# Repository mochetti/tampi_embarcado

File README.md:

# Tampi Embarcado

Programas para o NodeMCU embarcado no Tampi.

Todos os arquivos são compatíveis com a IDE Arduino.

## Contribuição

Todas as sugestões são bem vindas. Caso encontre um bug, fique à vontade para [abrir uma issue](https://github.com/mochetti/tampi_embarcado/issues/new).

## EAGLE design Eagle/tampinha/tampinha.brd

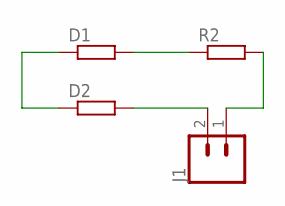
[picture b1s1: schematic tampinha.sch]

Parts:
D1, D2: R-EU_0204/7; 0204/7
J1: CONN_02; 1X02
R2: R-EU_0204/7; 0204/7

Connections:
unnamed: D1.2, R2.1
unnamed: D1.1, D2.1
unnamed: D2.2, J1.2
unnamed: J1.1, R2.2

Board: 2 copper layers, 4 parts (0 on the bottom side), 4 nets, no tracks yet.

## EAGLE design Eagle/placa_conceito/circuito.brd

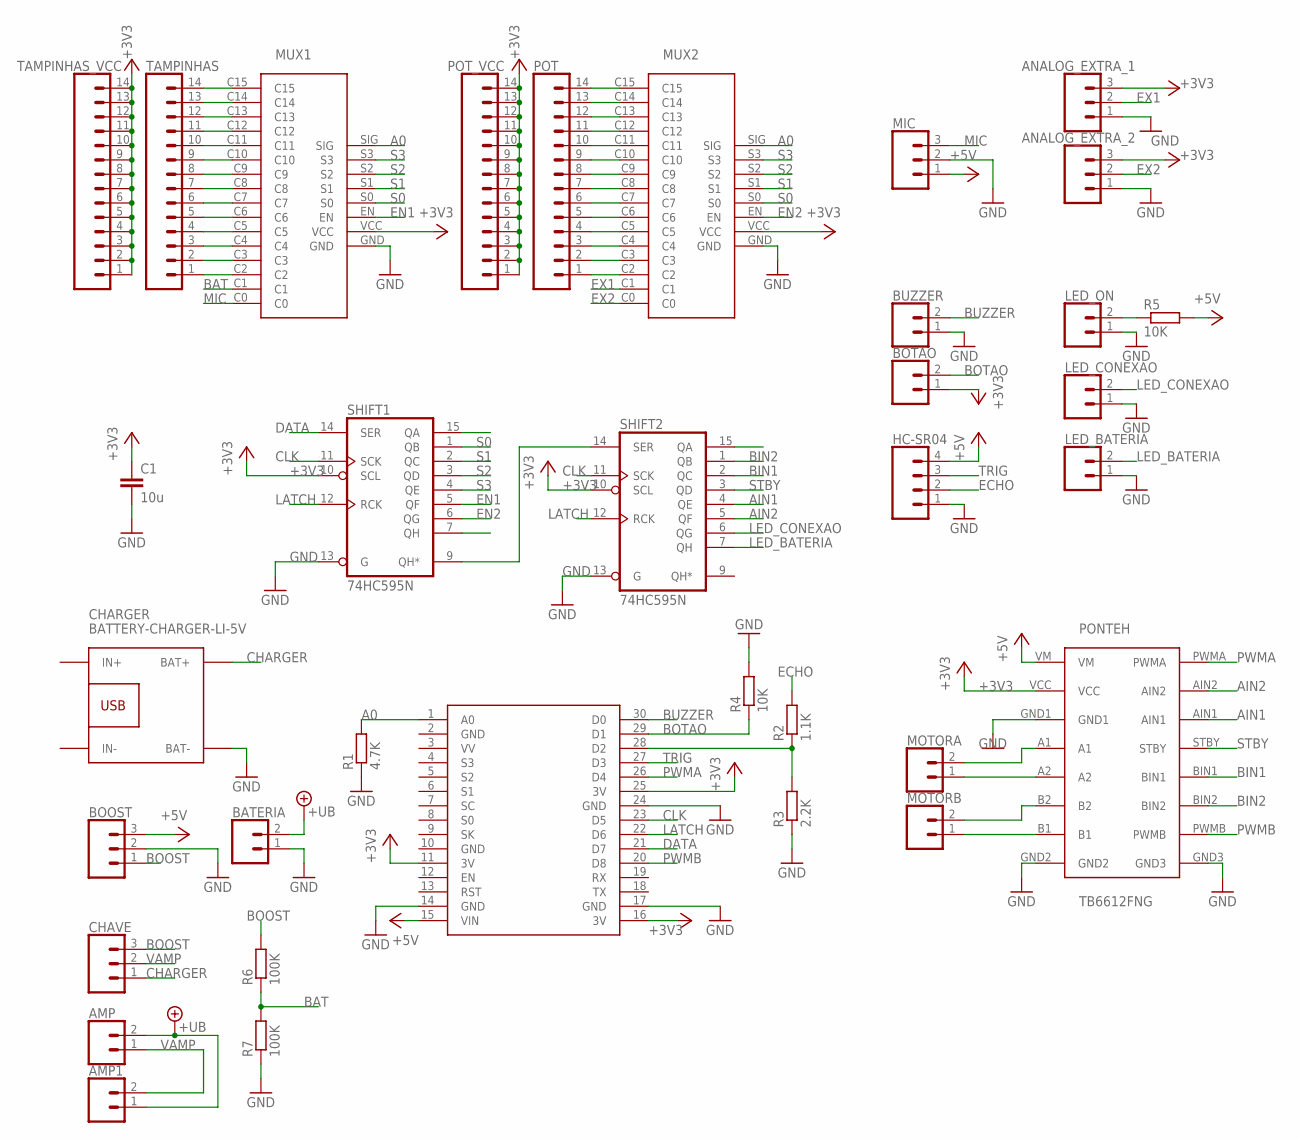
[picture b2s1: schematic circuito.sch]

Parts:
AMP, AMP1: CONN_02; 1X02
ANALOG_EXTRA_1, ANALOG_EXTRA_2: CONN_03; 1X03
BATERIA: CONN_02; 1X02
BOOST: CONN_03; 1X03
BOTAO: CONN_02; 1X02
BUZZER: CONN_02; 1X02
C1: 10u; C2.5-3
CHARGER: BATTERY-CHARGER-LI-5V
CHAVE: CONN_03; 1X03
HC-SR04: CONN_04; 1X04
LED_BATERIA: CONN_02; 1X02
LED_CONEXAO: CONN_02; 1X02
LED_ON: CONN_02; 1X02
MIC: CONN_03; 1X03
MOTORA: CONN_02; 1X02
MOTORB: CONN_02; 1X02
MUX1, MUX2: 4067_MODULE
NODEMCU: NODEMCU
PONTEH: TB6612FNG
POT: CONN_14; 1X14
POT_VCC: CONN_14; 1X14
R1: 4.7K; 0204/7
R2: 1.1K; 0204/7
R3: 2.2K; 0204/7
R4, R5: 10K; 0204/7
R6, R7: 100K; 0204/7
SHIFT1, SHIFT2: 74HC595N; DIL16
TAMPINHAS: CONN_14; 1X14
TAMPINHAS_VCC: CONN_14; 1X14

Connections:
+3V3: ANALOG_EXTRA_1.3, ANALOG_EXTRA_2.3, BOTAO.1, C1.1, MUX1.VCC, MUX2.VCC, NODEMCU.11 (3V), NODEMCU.16 (3V), NODEMCU.25 (3V), PONTEH.VCC, POT_VCC.1, POT_VCC.2, POT_VCC.3, POT_VCC.4, POT_VCC.5, POT_VCC.6, POT_VCC.7, POT_VCC.8, POT_VCC.9, POT_VCC.10, POT_VCC.11, POT_VCC.12, POT_VCC.13, POT_VCC.14, SHIFT1.10 (SCL), SHIFT2.10 (SCL), TAMPINHAS_VCC.1, TAMPINHAS_VCC.2, TAMPINHAS_VCC.3, TAMPINHAS_VCC.4, TAMPINHAS_VCC.5, TAMPINHAS_VCC.6, TAMPINHAS_VCC.7, TAMPINHAS_VCC.8, TAMPINHAS_VCC.9, TAMPINHAS_VCC.10, TAMPINHAS_VCC.11, TAMPINHAS_VCC.12, TAMPINHAS_VCC.13, TAMPINHAS_VCC.14
+5V: BOOST.3, HC-SR04.4, MIC.1, NODEMCU.15 (VIN), PONTEH.VM, R5.2
+UB: AMP.2, AMP1.1, BATERIA.2
A0: MUX1.SIG, MUX2.SIG, NODEMCU.1 (A0), R1.2
AIN1: PONTEH.AIN1, SHIFT2.4 (QE)
AIN2: PONTEH.AIN2, SHIFT2.5 (QF)
BAT: MUX1.C1, R6.1, R7.2
BIN1: PONTEH.BIN1, SHIFT2.2 (QC)
BIN2: PONTEH.BIN2, SHIFT2.1 (QB)
BOOST: BOOST.1, CHAVE.3, R6.2
BOTAO: BOTAO.2, NODEMCU.29 (D1), R4.1
BUZZER: BUZZER.2, NODEMCU.30 (D0)
CHARGER: CHARGER.BAT+, CHAVE.1
CLK: NODEMCU.23 (D5), SHIFT1.11 (SCK), SHIFT2.11 (SCK)
DATA: NODEMCU.21 (D7), SHIFT1.14 (SER)
ECHO: HC-SR04.2, R2.2
EN1: MUX1.EN, SHIFT1.5 (QF)
EN2: MUX2.EN, SHIFT1.6 (QG)
EX1: ANALOG_EXTRA_1.2, MUX2.C1
EX2: ANALOG_EXTRA_2.2, MUX2.C0
GND: ANALOG_EXTRA_1.1, ANALOG_EXTRA_2.1, BATERIA.1, BOOST.2, BUZZER.1, C1.2, CHARGER.BAT-, HC-SR04.1, LED_BATERIA.1, LED_CONEXAO.1, LED_ON.1, MIC.2, MUX1.GND, MUX2.GND, NODEMCU.2 (GND), NODEMCU.10 (GND), NODEMCU.14 (GND), NODEMCU.17 (GND), NODEMCU.24 (GND), PONTEH.GND1, PONTEH.GND2, PONTEH.GND3, R1.1, R3.1, R4.2, R7.1, SHIFT1.8 (GND), SHIFT1.13 (G), SHIFT2.8 (GND), SHIFT2.13 (G)
LATCH: NODEMCU.22 (D6), SHIFT1.12 (RCK), SHIFT2.12 (RCK)
LED_BATERIA: LED_BATERIA.2, SHIFT2.7 (QH)
LED_CONEXAO: LED_CONEXAO.2, SHIFT2.6 (QG)
MIC: MIC.3, MUX1.C0
unnamed: MOTORA.2, PONTEH.A1
unnamed: MOTORA.1, PONTEH.A2
unnamed: MOTORB.2, PONTEH.B2
unnamed: MOTORB.1, PONTEH.B1
unnamed: SHIFT1.9 (QH*), SHIFT2.14 (SER)
unnamed: MUX2.C2, POT.1
unnamed: MUX2.C3, POT.2
unnamed: MUX2.C4, POT.3
unnamed: MUX2.C5, POT.4
unnamed: MUX2.C6, POT.5
unnamed: MUX2.C7, POT.6
unnamed: MUX2.C8, POT.7
unnamed: MUX2.C9, POT.8
unnamed: MUX2.C10, POT.9
unnamed: MUX2.C11, POT.10
unnamed: MUX2.C12, POT.11
unnamed: MUX2.C13, POT.12
unnamed: MUX2.C14, POT.13
unnamed: MUX2.C15, POT.14
unnamed: MUX1.C2, TAMPINHAS.1
unnamed: MUX1.C3, TAMPINHAS.2
unnamed: MUX1.C4, TAMPINHAS.3
unnamed: MUX1.C5, TAMPINHAS.4
unnamed: MUX1.C6, TAMPINHAS.5
unnamed: MUX1.C7, TAMPINHAS.6
unnamed: MUX1.C8, TAMPINHAS.7
unnamed: MUX1.C9, TAMPINHAS.8
unnamed: MUX1.C10, TAMPINHAS.9
unnamed: MUX1.C11, TAMPINHAS.10
unnamed: MUX1.C12, TAMPINHAS.11
unnamed: MUX1.C13, TAMPINHAS.12
unnamed: MUX1.C14, TAMPINHAS.13
unnamed: MUX1.C15, TAMPINHAS.14
unnamed: NODEMCU.28 (D2), R2.1, R3.2
unnamed: LED_ON.2, R5.1
PWMA: NODEMCU.26 (D4), PONTEH.PWMA
PWMB: NODEMCU.20 (D8), PONTEH.PWMB
S0: MUX1.S0, MUX2.S0, SHIFT1.1 (QB)
S1: MUX1.S1, MUX2.S1, SHIFT1.2 (QC)
S2: MUX1.S2, MUX2.S2, SHIFT1.3 (QD)
S3: MUX1.S3, MUX2.S3, SHIFT1.4 (QE)
STBY: PONTEH.STBY, SHIFT2.3 (QD)
TRIG: HC-SR04.3, NODEMCU.27 (D3)
VAMP: AMP.1, AMP1.2, CHAVE.2
VCC: SHIFT1.16 (VCC), SHIFT2.16 (VCC)

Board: 2 copper layers, 35 parts (0 on the bottom side), 70 nets, no tracks yet.

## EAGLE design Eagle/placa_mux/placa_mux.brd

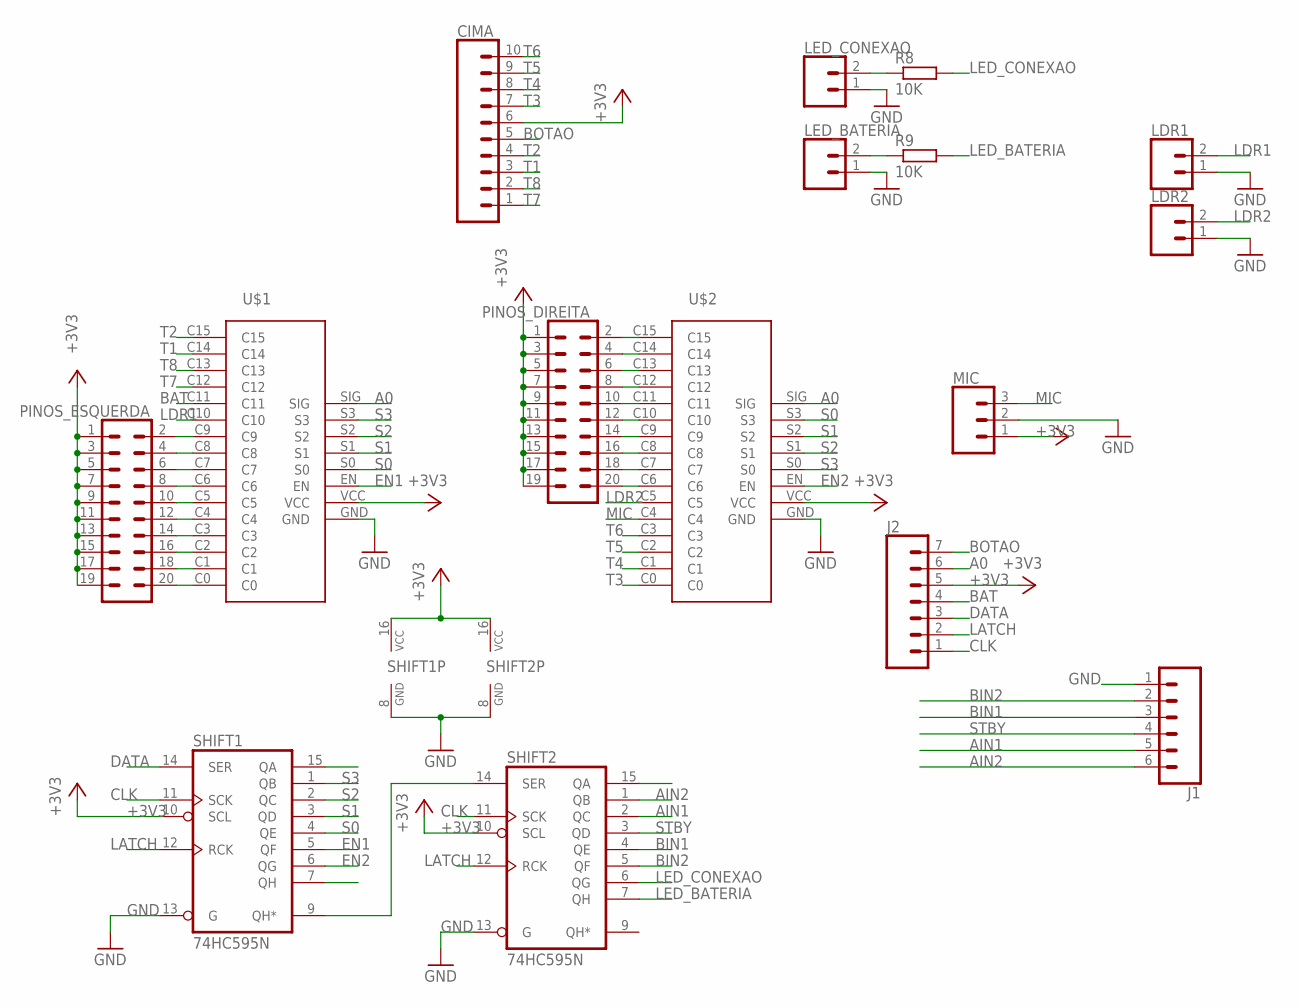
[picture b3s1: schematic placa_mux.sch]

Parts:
CIMA: CONN_10"; 1X10
J1: CONN_06SILK_FEMALE_PTH; 1X06
J2: CONN_07; 1X07
LDR1, LDR2: CONN_02; 1X02
LED_BATERIA: CONN_02; 1X02
LED_CONEXAO: CONN_02; 1X02
MIC: CONN_03; 1X03
PINOS_DIREITA: CONN_10X2; 2X10
PINOS_ESQUERDA: CONN_10X2; 2X10
R8, R9: 10K; 0204/7
SHIFT1, SHIFT2: 74HC595N; DIL16
U$1, U$2: 4067_MODULE

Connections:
+3V3: CIMA.6, J2.5, MIC.1, PINOS_DIREITA.1, PINOS_DIREITA.3, PINOS_DIREITA.5, PINOS_DIREITA.7, PINOS_DIREITA.9, PINOS_DIREITA.11, PINOS_DIREITA.13, PINOS_DIREITA.15, PINOS_DIREITA.17, PINOS_DIREITA.19, PINOS_ESQUERDA.1, PINOS_ESQUERDA.3, PINOS_ESQUERDA.5, PINOS_ESQUERDA.7, PINOS_ESQUERDA.9, PINOS_ESQUERDA.11, PINOS_ESQUERDA.13, PINOS_ESQUERDA.15, PINOS_ESQUERDA.17, PINOS_ESQUERDA.19, SHIFT1.10 (SCL), SHIFT1.16 (VCC), SHIFT2.10 (SCL), SHIFT2.16 (VCC), U$1.VCC, U$2.VCC
A0: J2.6, U$1.SIG, U$2.SIG
AIN1: J1.5, SHIFT2.2 (QC)
AIN2: J1.6, SHIFT2.1 (QB)
BAT: J2.4, U$1.C11
BIN1: J1.3, SHIFT2.4 (QE)
BIN2: J1.2, SHIFT2.5 (QF)
BOTAO: CIMA.5, J2.7
CLK: J2.1, SHIFT1.11 (SCK), SHIFT2.11 (SCK)
DATA: J2.3, SHIFT1.14 (SER)
EN1: SHIFT1.5 (QF), U$1.EN
EN2: SHIFT1.6 (QG), U$2.EN
GND: J1.1, LDR1.1, LDR2.1, LED_BATERIA.1, LED_CONEXAO.1, MIC.2, SHIFT1.8 (GND), SHIFT1.13 (G), SHIFT2.8 (GND), SHIFT2.13 (G), U$1.GND, U$2.GND
LATCH: J2.2, SHIFT1.12 (RCK), SHIFT2.12 (RCK)
LDR1: LDR1.2, U$1.C10
LDR2: LDR2.2, U$2.C5
LED_BATERIA: R9.2, SHIFT2.7 (QH)
LED_CONEXAO: R8.2, SHIFT2.6 (QG)
MIC: MIC.3, U$2.C4
unnamed: PINOS_ESQUERDA.2, U$1.C9
unnamed: PINOS_ESQUERDA.4, U$1.C8
unnamed: PINOS_ESQUERDA.6, U$1.C7
unnamed: PINOS_ESQUERDA.8, U$1.C6
unnamed: SHIFT1.9 (QH*), SHIFT2.14 (SER)
unnamed: PINOS_ESQUERDA.10, U$1.C5
unnamed: PINOS_ESQUERDA.12, U$1.C4
unnamed: PINOS_DIREITA.2, U$2.C15
unnamed: PINOS_DIREITA.4, U$2.C14
unnamed: PINOS_DIREITA.6, U$2.C13
unnamed: PINOS_DIREITA.8, U$2.C12
unnamed: PINOS_DIREITA.10, U$2.C11
unnamed: PINOS_DIREITA.12, U$2.C10
unnamed: PINOS_DIREITA.14, U$2.C9
unnamed: PINOS_DIREITA.16, U$2.C8
unnamed: PINOS_DIREITA.18, U$2.C7
unnamed: PINOS_DIREITA.20, U$2.C6
unnamed: PINOS_ESQUERDA.14, U$1.C3
unnamed: PINOS_ESQUERDA.16, U$1.C2
unnamed: PINOS_ESQUERDA.18, U$1.C1
unnamed: PINOS_ESQUERDA.20, U$1.C0
unnamed: LED_CONEXAO.2, R8.1
unnamed: LED_BATERIA.2, R9.1
S0: SHIFT1.4 (QE), U$1.S0, U$2.S3
S1: SHIFT1.3 (QD), U$1.S1, U$2.S2
S2: SHIFT1.2 (QC), U$1.S2, U$2.S1
S3: SHIFT1.1 (QB), U$1.S3, U$2.S0
STBY: J1.4, SHIFT2.3 (QD)
T1: CIMA.3, U$1.C14
T2: CIMA.4, U$1.C15
T3: CIMA.7, U$2.C0
T4: CIMA.8, U$2.C1
T5: CIMA.9, U$2.C2
T6: CIMA.10, U$2.C3
T7: CIMA.1, U$1.C12
T8: CIMA.2, U$1.C13

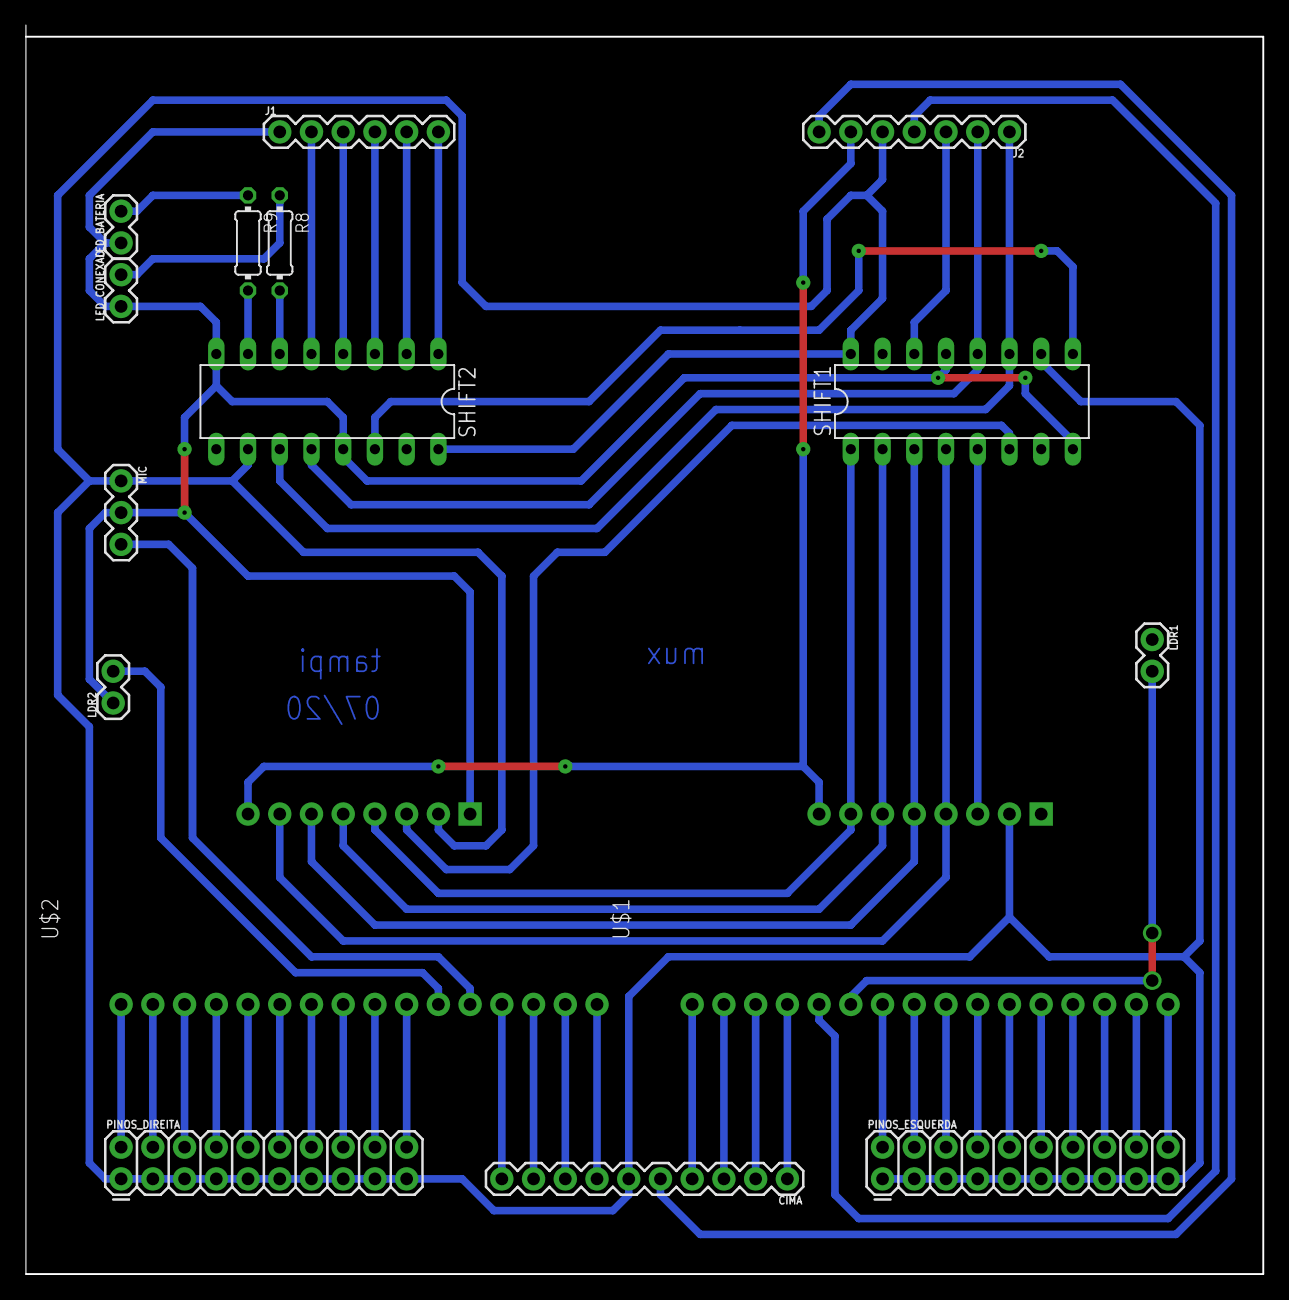
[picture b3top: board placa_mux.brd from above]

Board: 2 copper layers, 99.1 x 100.0 mm, 16 parts (0 on the bottom side), 55 nets.

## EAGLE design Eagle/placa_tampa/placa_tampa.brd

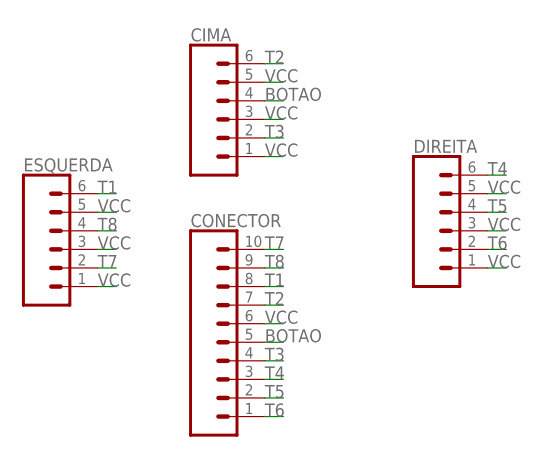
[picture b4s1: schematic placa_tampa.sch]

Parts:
CIMA: CONN_06SILK_FEMALE_PTH; 1X06
CONECTOR: CONN_10"; 1X10
DIREITA: CONN_06SILK_FEMALE_PTH; 1X06
ESQUERDA: CONN_06SILK_FEMALE_PTH; 1X06

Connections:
BOTAO: CIMA.4, CONECTOR.5
T1: CONECTOR.8, ESQUERDA.6
T2: CIMA.6, CONECTOR.7
T3: CIMA.2, CONECTOR.4
T4: CONECTOR.3, DIREITA.6
T5: CONECTOR.2, DIREITA.4
T6: CONECTOR.1, DIREITA.2
T7: CONECTOR.10, ESQUERDA.2
T8: CONECTOR.9, ESQUERDA.4
VCC: CIMA.1, CIMA.3, CIMA.5, CONECTOR.6, DIREITA.1, DIREITA.3, DIREITA.5, ESQUERDA.1, ESQUERDA.3, ESQUERDA.5

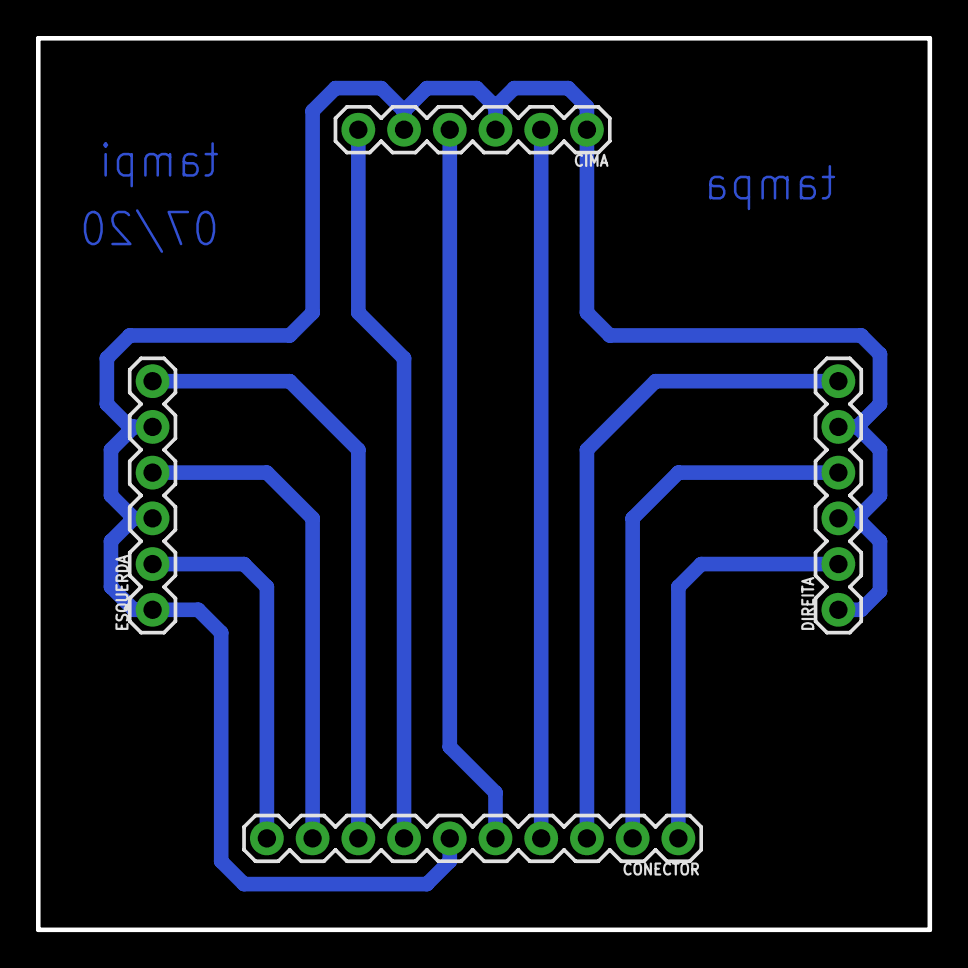
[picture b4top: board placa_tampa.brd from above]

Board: 2 copper layers, 49.5 x 49.5 mm, 4 parts (0 on the bottom side), 10 nets.

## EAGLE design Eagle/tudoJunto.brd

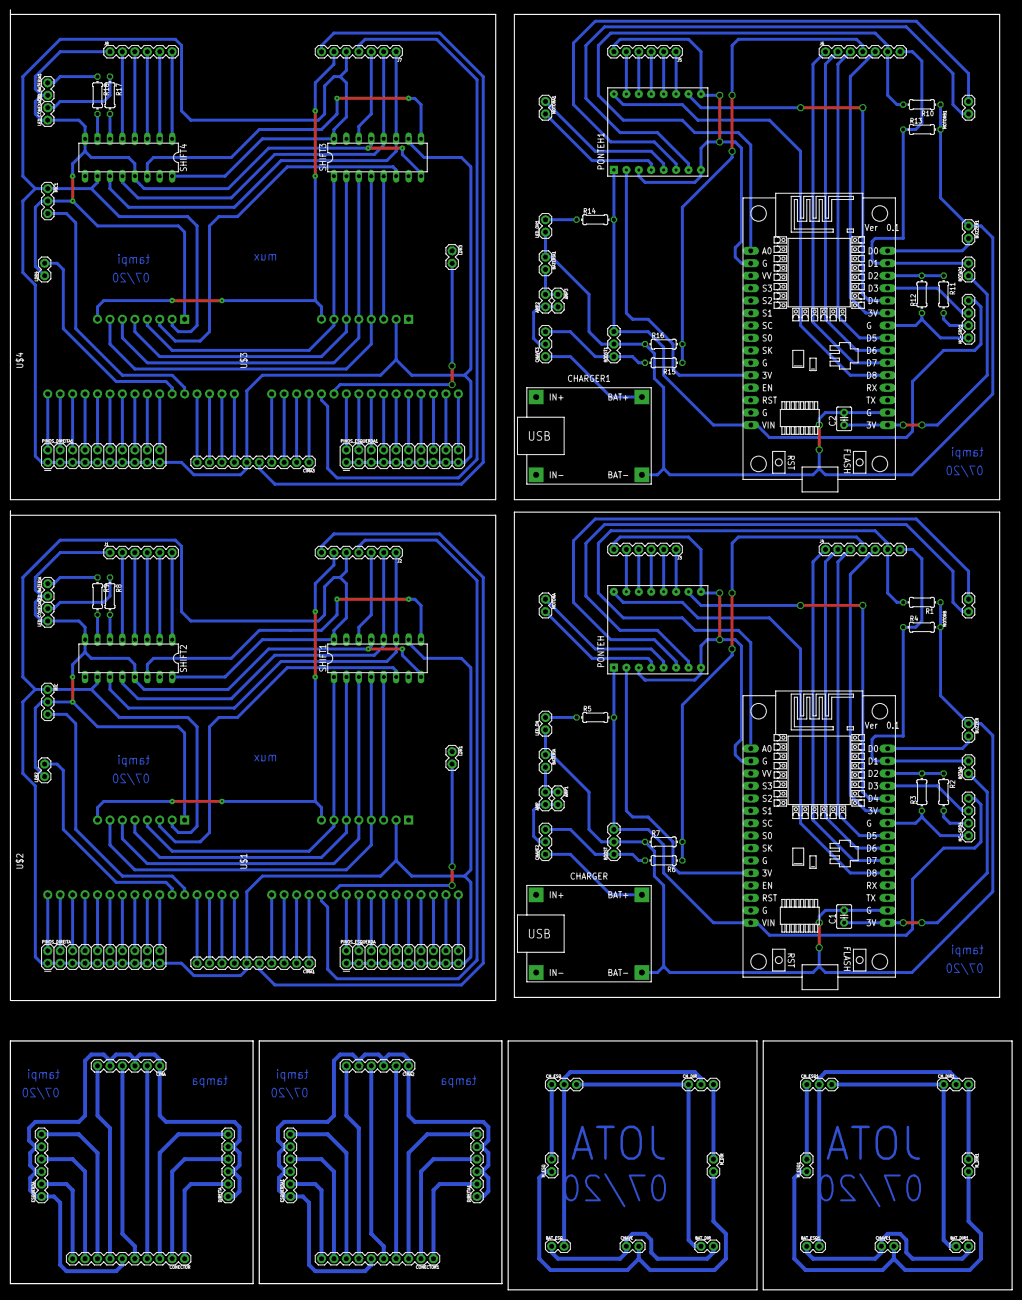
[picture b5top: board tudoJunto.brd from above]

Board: 2 copper layers, 204.5 x 261.3 mm, 102 parts (0 on the bottom side), 200 nets.

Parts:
AMP, AMP1, AMP2, AMP3: 1X02
BATERIA, BATERIA1: 1X02
BAT_DIR, BAT_DIR1: 1X02
BAT_ESQ, BAT_ESQ1: 1X02
BOOST, BOOST1: 1X03
BOTAO, BOTAO1: 1X02
BUZZER, BUZZER1: 1X02
C1, C2: 10u; C2.5-3
CHARGER, CHARGER1: BATTERY-CHARGER-LI-5V
CHAVE, CHAVE1: 1X02
CHAVE2, CHAVE3: 1X03
CH_DIR, CH_DIR1: 1X03
CH_ESQ, CH_ESQ1: 1X03
CIMA, CIMA2: 1X06
CIMA1, CIMA3: 1X10
CONECTOR, CONECTOR1: 1X10
DIREITA, DIREITA1: 1X06
ESQUERDA, ESQUERDA1: 1X06
HC-SR01, HC-SR04: 1X04
J1, J3, J5, J8: 1X06
J2, J4, J6, J7: 1X07
LDR1, LDR2, LDR3, LDR4: 1X02
LED_BATERIA, LED_BATERIA1: 1X02
LED_CONEXAO, LED_CONEXAO1: 1X02
LED_ON, LED_ON1: 1X02
MIC, MIC1: 1X03
MOTORA, MOTORA1: 1X02
MOTORB, MOTORB1: 1X02
M_DIR, M_DIR1: 1X02
M_ESQ, M_ESQ1: 1X02
NODEMCU, NODEMCU1: NODEMCU
PINOS_DIREITA, PINOS_DIREITA1: 2X10
PINOS_ESQUERDA, PINOS_ESQUERDA1: 2X10
PONTEH, PONTEH1: TB6612FNG
R1, R10: 4.7K; 0204/7
R2, R11: 1.1K; 0204/7
R3, R12: 2.2K; 0204/7
R4, R5, R8, R9, R13, R14, R17, R18: 10K; 0204/7
R6, R7, R15, R16: 100K; 0204/7
SHIFT1, SHIFT2, SHIFT3, SHIFT4: 74HC595N; DIL16
U$1, U$2, U$3, U$4: 4067_MODULE

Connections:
+3V1: BOTAO.1, C1.1, J4.5, NODEMCU.11, NODEMCU.16, NODEMCU.25, PONTEH.VCC
+3V2: BOTAO1.1, C2.1, J6.5, NODEMCU1.11, NODEMCU1.16, NODEMCU1.25, PONTEH1.VCC
+3V3: CIMA1.6, J2.5, MIC.1, PINOS_DIREITA.1, PINOS_DIREITA.3, PINOS_DIREITA.5, PINOS_DIREITA.7, PINOS_DIREITA.9, PINOS_DIREITA.11, PINOS_DIREITA.13, PINOS_DIREITA.15, PINOS_DIREITA.17, PINOS_DIREITA.19, PINOS_ESQUERDA.1, PINOS_ESQUERDA.3, PINOS_ESQUERDA.5, PINOS_ESQUERDA.7, PINOS_ESQUERDA.9, PINOS_ESQUERDA.11, PINOS_ESQUERDA.13, PINOS_ESQUERDA.15, PINOS_ESQUERDA.17, PINOS_ESQUERDA.19, SHIFT1.10, SHIFT1.16, SHIFT2.10, SHIFT2.16, U$1.VCC, U$2.VCC
+3V4: CIMA3.6, J7.5, MIC1.1, PINOS_DIREITA1.1, PINOS_DIREITA1.3, PINOS_DIREITA1.5, PINOS_DIREITA1.7, PINOS_DIREITA1.9, PINOS_DIREITA1.11, PINOS_DIREITA1.13, PINOS_DIREITA1.15, PINOS_DIREITA1.17, PINOS_DIREITA1.19, PINOS_ESQUERDA1.1, PINOS_ESQUERDA1.3, PINOS_ESQUERDA1.5, PINOS_ESQUERDA1.7, PINOS_ESQUERDA1.9, PINOS_ESQUERDA1.11, PINOS_ESQUERDA1.13, PINOS_ESQUERDA1.15, PINOS_ESQUERDA1.17, PINOS_ESQUERDA1.19, SHIFT3.10, SHIFT3.16, SHIFT4.10, SHIFT4.16, U$3.VCC, U$4.VCC
+5V: BOOST.3, HC-SR04.4, NODEMCU.15, PONTEH.VM, R5.2
+5V1: BOOST1.3, HC-SR01.4, NODEMCU1.15, PONTEH1.VM, R14.2
+UB: AMP.2, AMP1.1, BATERIA.2
+UB1: AMP2.2, AMP3.1, BATERIA1.2
A0: J2.6, U$1.SIG, U$2.SIG
A1: J4.6, NODEMCU.1, R1.2
A2: J6.6, NODEMCU1.1, R10.2
A3: J7.6, U$3.SIG, U$4.SIG
AIN1: J1.5, SHIFT2.2
AIN2: J1.6, SHIFT2.1
AIN3: J3.5, PONTEH.AIN2
AIN4: J3.4, PONTEH.AIN1
AIN5: J5.5, PONTEH1.AIN2
AIN6: J5.4, PONTEH1.AIN1
AIN7: J8.6, SHIFT4.1
AIN8: J8.5, SHIFT4.2
BAT: J2.4, U$1.C11
BAT1: J4.4, R6.1, R7.2
BAT2: J6.4, R15.1, R16.2
BAT3: J7.4, U$3.C11
BIN1: J1.3, SHIFT2.4
BIN2: J1.2, SHIFT2.5
BIN3: J3.2, PONTEH.BIN1
BIN4: J3.1, PONTEH.BIN2
BIN5: J5.2, PONTEH1.BIN1
BIN6: J5.1, PONTEH1.BIN2
BIN7: J8.3, SHIFT4.4
BIN8: J8.2, SHIFT4.5
BOOST: BOOST.1, CHAVE2.3, R6.2
BOOST1: BOOST1.1, CHAVE3.3, R15.2
BOTAO: CIMA.4, CONECTOR.5
BOTAO1: CIMA1.5, J2.7
BOTAO2: CIMA2.4, CONECTOR1.5
BOTAO3: BOTAO.2, J4.7, NODEMCU.29, R4.1
BOTAO4: BOTAO1.2, J6.7, NODEMCU1.29, R13.1
BOTAO5: CIMA3.5, J7.7
BUZZER: BUZZER.2, NODEMCU.30
BUZZER1: BUZZER1.2, NODEMCU1.30
CHARGER: CHARGER.BAT+, CHAVE2.1
CHARGER1: CHARGER1.BAT+, CHAVE3.1
CLK: J2.1, SHIFT1.11, SHIFT2.11
CLK1: J4.1, NODEMCU.21
CLK2: J6.1, NODEMCU1.21
CLK3: J7.1, SHIFT3.11, SHIFT4.11
DATA: J2.3, SHIFT1.14
DATA1: J4.3, NODEMCU.23
DATA2: J6.3, NODEMCU1.23
DATA3: J7.3, SHIFT3.14
ECHO: HC-SR04.2, R2.2
ECHO1: HC-SR01.2, R11.2
EN1: SHIFT1.5, U$1.EN
EN2: SHIFT1.6, U$2.EN
EN3: SHIFT3.5, U$3.EN
EN4: SHIFT3.6, U$4.EN
GND1: J1.1, LDR1.1, LDR2.1, LED_BATERIA.1, LED_CONEXAO.1, MIC.2, SHIFT1.8, SHIFT1.13, SHIFT2.8, SHIFT2.13, U$1.GND, U$2.GND
GND5: BATERIA.1, BOOST.2, BUZZER.1, C1.2, CHARGER.BAT-, HC-SR04.1, J3.6, LED_ON.1, NODEMCU.2, NODEMCU.10, NODEMCU.14, NODEMCU.17, NODEMCU.24, PONTEH.GND1, PONTEH.GND2, PONTEH.GND3, R1.1, R3.1, R4.2, R7.1
GND6: BATERIA1.1, BOOST1.2, BUZZER1.1, C2.2, CHARGER1.BAT-, HC-SR01.1, J5.6, LED_ON1.1, NODEMCU1.2, NODEMCU1.10, NODEMCU1.14, NODEMCU1.17, NODEMCU1.24, PONTEH1.GND1, PONTEH1.GND2, PONTEH1.GND3, R10.1, R12.1, R13.2, R16.1
GND7: J8.1, LDR3.1, LDR4.1, LED_BATERIA1.1, LED_CONEXAO1.1, MIC1.2, SHIFT3.8, SHIFT3.13, SHIFT4.8, SHIFT4.13, U$3.GND, U$4.GND
LATCH: J2.2, SHIFT1.12, SHIFT2.12
LATCH1: J4.2, NODEMCU.22
LATCH2: J6.2, NODEMCU1.22
LATCH3: J7.2, SHIFT3.12, SHIFT4.12
LDR1: LDR1.2, U$1.C10
LDR2: LDR2.2, U$2.C5
LDR3: LDR3.2, U$3.C10
LDR4: LDR4.2, U$4.C5
LED_BATERIA: R9.2, SHIFT2.7
LED_BATERIA1: R18.2, SHIFT4.7
LED_CONEXAO: R8.2, SHIFT2.6
LED_CONEXAO1: R17.2, SHIFT4.6
MIC: MIC.3, U$2.C4
MIC1: MIC1.3, U$4.C4
unnamed: PINOS_ESQUERDA.2, U$1.C9
unnamed: PINOS_ESQUERDA.4, U$1.C8
unnamed: PINOS_ESQUERDA.6, U$1.C7
unnamed: PINOS_ESQUERDA.8, U$1.C6
unnamed: SHIFT1.9, SHIFT2.14
unnamed: PINOS_ESQUERDA.10, U$1.C5
unnamed: PINOS_ESQUERDA.12, U$1.C4
unnamed: PINOS_DIREITA.2, U$2.C15
unnamed: PINOS_DIREITA.4, U$2.C14
unnamed: PINOS_DIREITA.6, U$2.C13
unnamed: PINOS_DIREITA.8, U$2.C12
unnamed: PINOS_DIREITA.10, U$2.C11
unnamed: PINOS_DIREITA.12, U$2.C10
unnamed: PINOS_DIREITA.14, U$2.C9
unnamed: PINOS_DIREITA.16, U$2.C8
unnamed: PINOS_DIREITA.18, U$2.C7
unnamed: PINOS_DIREITA.20, U$2.C6
unnamed: PINOS_ESQUERDA.14, U$1.C3
unnamed: PINOS_ESQUERDA.16, U$1.C2
unnamed: PINOS_ESQUERDA.18, U$1.C1
unnamed: PINOS_ESQUERDA.20, U$1.C0
unnamed: LED_CONEXAO.2, R8.1
unnamed: LED_BATERIA.2, R9.1
unnamed: BAT_ESQ.2, CH_DIR.2, CH_ESQ.2
unnamed: BAT_DIR.1, CH_DIR.1, CH_ESQ.3
unnamed: CH_DIR.3, M_DIR.1
unnamed: CH_ESQ.1, M_ESQ.2
unnamed: CHAVE.2, M_DIR.2, M_ESQ.1
unnamed: BAT_DIR.2, BAT_ESQ.1, CHAVE.1
unnamed: BAT_ESQ1.2, CH_DIR1.2, CH_ESQ1.2
unnamed: BAT_DIR1.1, CH_DIR1.1, CH_ESQ1.3
unnamed: CH_DIR1.3, M_DIR1.1
unnamed: CH_ESQ1.1, M_ESQ1.2
unnamed: CHAVE1.2, M_DIR1.2, M_ESQ1.1
unnamed: BAT_DIR1.2, BAT_ESQ1.1, CHAVE1.1
unnamed: MOTORB.2, PONTEH.B2
unnamed: MOTORB.1, PONTEH.B1
unnamed: MOTORA.2, PONTEH.A1
unnamed: MOTORA.1, PONTEH.A2
unnamed: NODEMCU.28, R2.1, R3.2
unnamed: LED_ON.2, R5.1
unnamed: MOTORB1.2, PONTEH1.B2
unnamed: MOTORB1.1, PONTEH1.B1
unnamed: MOTORA1.2, PONTEH1.A1
unnamed: MOTORA1.1, PONTEH1.A2
unnamed: NODEMCU1.28, R11.1, R12.2
unnamed: LED_ON1.2, R14.1
unnamed: SHIFT3.9, SHIFT4.14
unnamed: PINOS_ESQUERDA1.2, U$3.C9
unnamed: PINOS_ESQUERDA1.4, U$3.C8
unnamed: PINOS_ESQUERDA1.6, U$3.C7
unnamed: PINOS_ESQUERDA1.8, U$3.C6
unnamed: PINOS_ESQUERDA1.10, U$3.C5
unnamed: PINOS_ESQUERDA1.12, U$3.C4
unnamed: PINOS_ESQUERDA1.14, U$3.C3
unnamed: PINOS_ESQUERDA1.16, U$3.C2
unnamed: PINOS_ESQUERDA1.18, U$3.C1
unnamed: PINOS_ESQUERDA1.20, U$3.C0
unnamed: PINOS_DIREITA1.2, U$4.C15
unnamed: PINOS_DIREITA1.4, U$4.C14
unnamed: PINOS_DIREITA1.6, U$4.C13
unnamed: PINOS_DIREITA1.8, U$4.C12
unnamed: PINOS_DIREITA1.10, U$4.C11
unnamed: PINOS_DIREITA1.12, U$4.C10
unnamed: PINOS_DIREITA1.14, U$4.C9
unnamed: PINOS_DIREITA1.16, U$4.C8
unnamed: PINOS_DIREITA1.18, U$4.C7
unnamed: PINOS_DIREITA1.20, U$4.C6
unnamed: LED_CONEXAO1.2, R17.1
unnamed: LED_BATERIA1.2, R18.1
PWMA: NODEMCU.20, PONTEH.PWMA
PWMA1: NODEMCU1.20, PONTEH1.PWMA
PWMB: NODEMCU.26, PONTEH.PWMB
PWMB1: NODEMCU1.26, PONTEH1.PWMB
S0: SHIFT1.4, U$1.S0, U$2.S3
S1: SHIFT1.3, U$1.S1, U$2.S2
S2: SHIFT1.2, U$1.S2, U$2.S1
S3: SHIFT1.1, U$1.S3, U$2.S0
S4: SHIFT3.1, U$3.S3, U$4.S0
S5: SHIFT3.2, U$3.S2, U$4.S1
S6: SHIFT3.3, U$3.S1, U$4.S2
S7: SHIFT3.4, U$3.S0, U$4.S3
STBY: J1.4, SHIFT2.3
STBY1: J3.3, PONTEH.STBY
STBY2: J5.3, PONTEH1.STBY
STBY3: J8.4, SHIFT4.3
T1: CONECTOR.8, ESQUERDA.6
T2: CIMA.6, CONECTOR.7
T3: CIMA.2, CONECTOR.4
T4: CONECTOR.3, DIREITA.6
T5: CONECTOR.2, DIREITA.4
T6: CONECTOR.1, DIREITA.2
T7: CONECTOR.10, ESQUERDA.2
T8: CONECTOR.9, ESQUERDA.4
T9: CIMA1.10, U$2.C3
T10: CIMA1.9, U$2.C2
T11: CIMA1.8, U$2.C1
T12: CIMA1.7, U$2.C0
T13: CIMA1.4, U$1.C15
T14: CIMA1.3, U$1.C14
T15: CIMA1.2, U$1.C13
T16: CIMA1.1, U$1.C12
T17: CONECTOR1.10, ESQUERDA1.2
T18: CONECTOR1.8, ESQUERDA1.6
T19: CIMA2.6, CONECTOR1.7
T20: CIMA2.2, CONECTOR1.4
T21: CONECTOR1.3, DIREITA1.6
T22: CONECTOR1.2, DIREITA1.4
T23: CONECTOR1.1, DIREITA1.2
T24: CONECTOR1.9, ESQUERDA1.4
T25: CIMA3.10, U$4.C3
T26: CIMA3.9, U$4.C2
T27: CIMA3.8, U$4.C1
T28: CIMA3.7, U$4.C0
T29: CIMA3.4, U$3.C15
T30: CIMA3.3, U$3.C14
T31: CIMA3.2, U$3.C13
T32: CIMA3.1, U$3.C12
TRIG: HC-SR04.3, NODEMCU.27
TRIG1: HC-SR01.3, NODEMCU1.27
VAMP: AMP.1, AMP1.2, CHAVE2.2
VAMP1: AMP2.1, AMP3.2, CHAVE3.2
VCC: CIMA.1, CIMA.3, CIMA.5, CONECTOR.6, DIREITA.1, DIREITA.3, DIREITA.5, ESQUERDA.1, ESQUERDA.3, ESQUERDA.5
VCC1: CIMA2.1, CIMA2.3, CIMA2.5, CONECTOR1.6, DIREITA1.1, DIREITA1.3, DIREITA1.5, ESQUERDA1.1, ESQUERDA1.3, ESQUERDA1.5

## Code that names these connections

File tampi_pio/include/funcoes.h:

#ifndef FUNCOES_H
#define FUNCOES_H

#include "Arduino.h"
#include <ESP8266WiFi.h>            // bibliotecas do servidor          
#include <WebSocketsServer.h>
// #include <WebSocketsClient.h>

// Pinos do NodeMCU

const int pwmEsq = D4;  // pinos digitais no ESP
const int pwmDir = D8;

const int echoPin = D2;  // echo do ultrassonico
const int trigPin = D3;  // trig do ultrassonico

const int dataPin = D5;  // dados seriais do 74595
const int latchPin = D6; // latch do 74595
const int clkPin = D7;   // clk do 74595

const int buzzerPin = D0;

const int botaoPin = D1;    // botao
const int analogPin = A0;  // pino analogico

// Pinos dos shifts

const int A4067 = 27;
const int B4067 = 28;
const int C4067 = 29;
const int D4067 = 30;
const int E4067 = 26;
const int F4067 = 25;

const int ledsTopo[] = {
  16, 17, 18, 19, 20, 21, 22, 23
};
const int ledsEsq[] = {
  38, 37, 36, 35, 34, 33
};
const int ledsDir[] = {
  14, 13, 12, 11, 10, 9
};

const int AIN2 = 4;
const int AIN1 = 3;
const int STDBY = 2;
const int BIN1 = 1;
const int BIN2 = 0;

const int redPin = 7;
const int greenPin = 6;
const int bluePin = 5;

const int farolPin = 24;
const int irEsqLED = 39;
const int irDirLED = 15;
const int setaEsqPin = 32;
const int setaDirPin = 8;

// Pinos dos mux

const int batPin = 1;
const int micPin = 16;
const int ldrEsqPin = 0;
const int ldrDirPin = 25;
const int encEsqPin = 2;
const int encDirPin = 23;
const int irEsqAnalog = 3;
const int irDirAnalog = 24;
const int tampinhasTopoPin[] = {
  10, 11, 12, 13, 19, 20, 21, 22
};
const int tampinhasEsqPin[] = {
  9, 8, 7, 6, 5, 4
};
const int tampinhasDirPin[] = {
  31, 30, 29, 28, 27, 26
};

const int analogExtra1 = 15;
const int analogExtra2 = 14;
const int analogExtra3 = 18;
const int analogExtra4 = 17;

// Variáveis globais

extern WebSocketsServer webSocket;  // servidor websocket
extern WiFiEventHandler stationConnectedHandler;
extern WiFiEventHandler stationDisconnectedHandler;

extern boolean wifi;
extern unsigned long tempo;
extern unsigned long ultimaConexao;

extern int pulsosEncoderEsq;
extern int pulsosEncoderDir;
extern bool encoderEsqPreto;
extern bool encoderDirPreto;
extern unsigned long tempoEncEsq;
extern unsigned long tempoEncDir;
extern int velEsq;
extern int velDir;

extern char sensores[30];

extern const char *ssid;
extern const char *password;

extern const char* mdnsName; // Domain name for the mDNS responder

extern byte shiftPinos[5];   // valores instantâneos dos pinos controlados pelos 74595
extern bool mudancaShiftPinos;   // controla se houve mudanca nos pinos dos 74595

extern int tampinhasTopo[8]; // array de acoes das tampinhas
extern int tampinhasEsq[6];
extern int tampinhasDir[6];

// Relação entre id das ações e cor da tampinha
extern const char *cores[];

// Relação de clientes configurados como PC
extern int pc[];
// Relação de clientes configurados como app
extern int app[];

extern const int velGeral;
extern const int tempoGiroEixo;

// Funções
void startAP();
void startWS();
void leituraSensores();
void dWrite(int, int);
void shift();
int aRead(int);
void musica(char *);
void motor(int, int);
void buzina(int);
void buzina(int, int);
void funcaoEsq();
void funcaoDir();
int classifica(int);
void encoders();
void conexaoCliente(const WiFiEventSoftAPModeStationConnected&);
void desconexaoCliente(const WiFiEventSoftAPModeStationDisconnected&);
String macToString(const unsigned char*);
void webSocketEvent(uint8_t, WStype_t, uint8_t *, size_t);
void freq();

#endif

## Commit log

2020-07-22 ESP add
2020-07-27 ajustes de hierarquia
2020-12-01 update files
2020-12-30 hierarquia
2021-01-07 WiFiEventHandler
2021-01-11 PlatformIO adicionado
2021-01-16 interno/externo
2021-02-05 pins update
2022-03-30 Bump guzzlehttp/psr7 from 1.6.1 to 1.8.5 in /Extra/websocket-python
    Bumps [guzzlehttp/psr7](https://github.com/guzzle/psr7) from 1.6.1 to 1.8.5.
    - [Release notes](https://github.com/guzzle/psr7/releases)
    - [Changelog](https://github.com/guzzle/psr7/blob/1.8.5/CHANGELOG.md)
    - [Commits](https://github.com/guzzle/psr7/compare/1.6.1...1.8.5)
    ---
    updated-dependencies:
2023-04-19 Bump guzzlehttp/psr7 from 1.6.1 to 1.9.1 in /Extra/websocket-python
    Bumps [guzzlehttp/psr7](https://github.com/guzzle/psr7) from 1.6.1 to 1.9.1.
    - [Release notes](https://github.com/guzzle/psr7/releases)
    - [Changelog](https://github.com/guzzle/psr7/blob/1.9.1/CHANGELOG.md)
    - [Commits](https://github.com/guzzle/psr7/compare/1.6.1...1.9.1)
    ---
    updated-dependencies:

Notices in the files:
parts and their libraries:
SparkFun-Connectors: Licensing: Creative Commons ShareAlike 4.0 International - https://creativecommons.org/licenses/by-sa/4.0
diy-modules: Released under the Creative Commons Attribution 4.0 International License: http://creativecommons.org/licenses/by/4.0
